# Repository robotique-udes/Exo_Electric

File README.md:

# Description
Ce répertoire regroupe les différents PCB de l'exosquelette au fil des compétitions. Il vise aussi à standardiser la création des schémas électriques ainsi que des PCB afin de les rendre plus lisibles et plus faciles à réviser et consulter. Les PCB avant 2026 ne suivent pas nécessairement le standard.

# Structure du repo
```
main
├── ACE2027/
│   ├── README.md
│   ├── Schéma-bloc
│   └── PCB1/
│       ├── README.md
│       ├── Schéma-bloc
│       │   ├── V1_0/
│       │   │   └── Fichiers KiCad
│       │   ├── V1_1/
│       │   │   ├── README.md
│       │   │   └── Fichiers KiCad
│       │   └── V2_0/
│       │       ├── README.md
│       │       └── Fichiers KiCad
│       └── PCB2/
│           └── (Même structure que PCB1)
└── ACE2028
    └── (Même structure que ACE 2027)
```
- Un dossier est créé pour chaque année de compétition
    - Contient un README.md décrivant le fonctionnement global du système électrique et présentant le schéma-bloc
    - Contient le schéma-bloc en image et dans son format original décrivant l'interaction entre les sous-systèmes électriques
    - Un dossier est créé par PCB
        - Contient un README.md qui explique le fonctionnement du PCB, contient les calculs et hypothèse fait pour le pcb et présente le schéma-bloc. Le README.md doit dire où se trouve le contour du pcb s'il a été fait sur ONSHAPE
        - Contient le schéma-bloc en image et dans son format original décrivant l'interaction entre les modules du PCB
            - Un dossier est fait pour chaque version du PCB.
                - La version 1_0 n'a pas besoin de README, mais les versions subséquentes devront en avoir un qui décrit les changements par rapport à la version antérieure.
                - Contient tous les fichiers KiCad

# Branches
Une branche est créée pour chaque PCB. <br>
Cette branche doit contenir le nom du PCB ainsi que sa version et le déroulement de la vie de cette branche se déroule ainsi:
1. Si le pcb est particuliairement complexe, écrire le readme et le shéma bloc qui défini ce que le PCB fait et comment il va le faire
2. Création d'une pull request vers le main afin de faire validé le fonctionnement du PCB
    - Faire les correctifs et demander à nouveau la vérification
3. Création du schéma électrique
4. Création d'une pull request vers le main afin de faire vérifier le schéma
    - Faire les correctifs et demander à nouveau la vérification
5. Création du PCB
6. Création d'une pull request vers le main afin de faire vérifier le PCB
    - Faire les correctifs et demander à nouveau la vérification
7. Suppression de la branche une fois le PCB commandé

## Convention de versions:
- V1.0  Premier prototype
- V1.X  Corrections mineures qui ne demandent pas de recommander le PCB
- VX.0  Révision majeure qui demande de recommander le PCB
- Chaque révision doit être documentée dans le README avec une explication claire des changements par rapport à la version précédente.

# Autres
**Il est très important de sauvegarder les fichiers et de fermer KiCad avant chaque commit**

# Standards à respecter
Les standards pour le schéma électrique se trouvent [ici](guideSchema.md) <br>
Les standards pour le PCB se trouvent [ici](guidePCB.md) <br>
Ces standards doivent être consultés et compris avant d'entamer le travail sur un schéma ou sur un PCB

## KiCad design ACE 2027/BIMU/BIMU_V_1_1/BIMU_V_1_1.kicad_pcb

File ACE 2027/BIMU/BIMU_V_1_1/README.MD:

## Update
* V1.1 
    inversé le RX et TX pour le CAN pour respecté les norme
    rajout une switch pour mettre ou retirer la therminaison CAN
    Connecté les deux pin de puissance du esp-32 qui doivent être connecté 
    fixer le silkscreen
    Rajouté des diodes pour évité le back feed dans le port USB

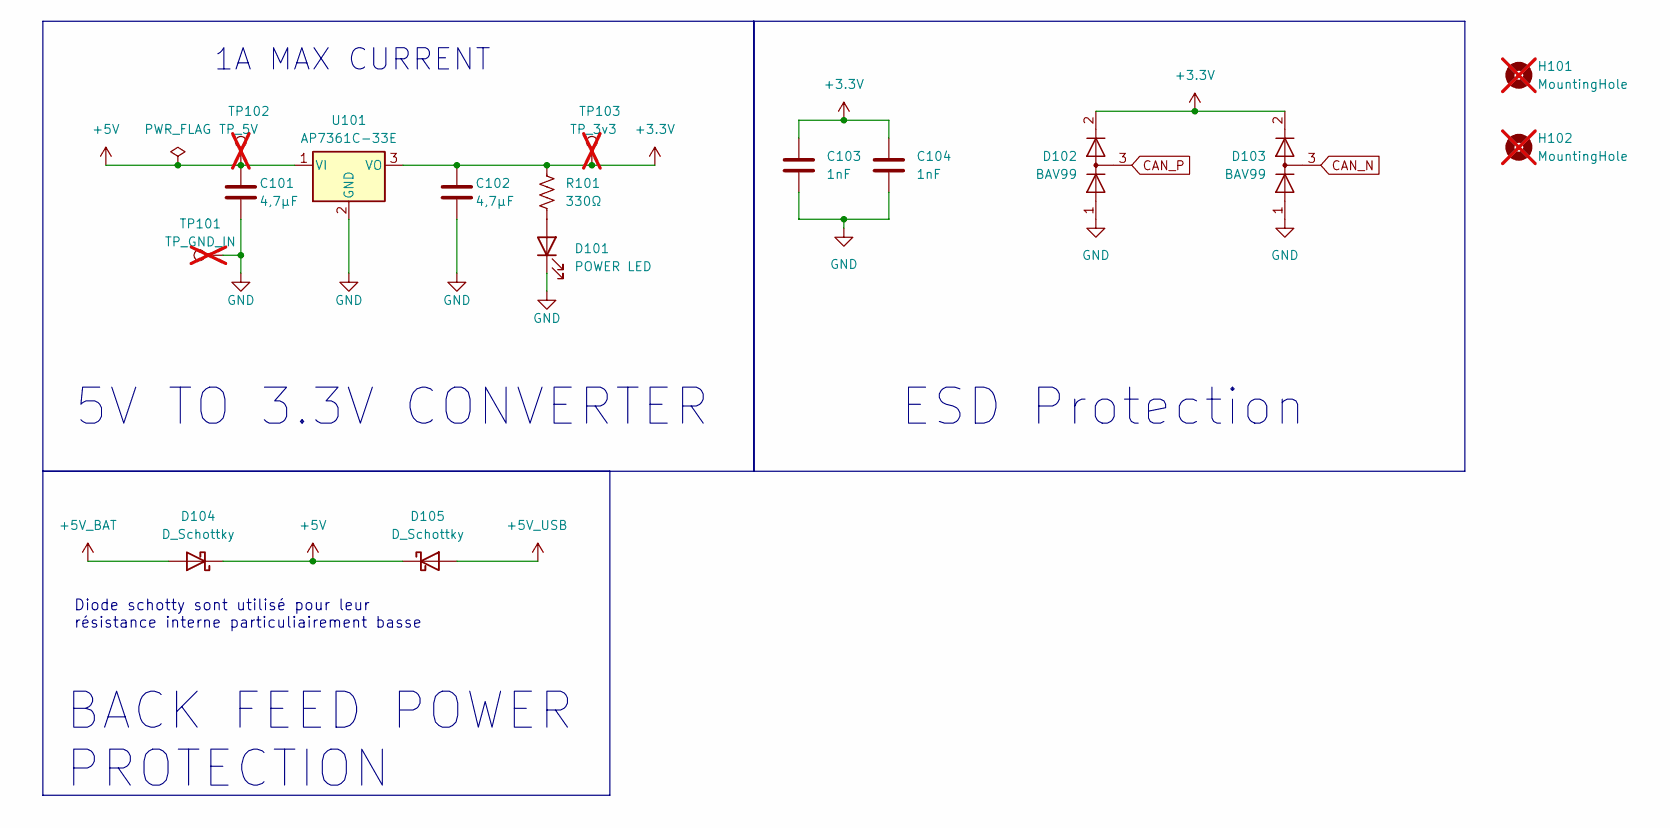
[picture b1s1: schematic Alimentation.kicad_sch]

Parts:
C101, C102: 4,7µF; C_0805_2012Metric_Pad1.18x1.45mm_HandSolder; Digi-Key_PN 1276-2970-1-ND
C103, C104: 1nF; C_1812_4532Metric_Pad1.57x3.40mm_HandSolder; Digi-Key_PN 399-C1812C104MDRACTUCT-ND
D101: POWER LED; LED_0805_2012Metric_Pad1.15x1.40mm_HandSolder; Digi-Key_PN 1516-QBLP631-IG5CT-ND
D102, D103: BAV99; SOT-23; Digi-Key_PN 1655-BAV99CT-ND
D104, D105: D_Schottky; D_0805_2012Metric_Pad1.15x1.40mm_HandSolder; Digi-Key_PN 478-7800-1-ND
H101, H102: MountingHole; MountingHole_3.2mm_M3_ISO14580; not fitted
R101: 330Ω; R_0805_2012Metric_Pad1.20x1.40mm_HandSolder; Digi-Key_PN 541-4168-1-ND
TP101: TP_GND_IN; TestPoint_Pad_1.0x1.0mm; not fitted
TP102: TP_5V; TestPoint_Pad_1.0x1.0mm; not fitted
TP103: TP_3v3; TestPoint_Pad_1.0x1.0mm; not fitted
U101: AP7361C-33E; SOT-223-3_TabPin2; Digi-Key_PN AP7361C-33E-13DICT-ND

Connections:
+3.3V: C102.2, C103.1, C104.1, D102.2 (A), D103.2 (A), R101.1, TP103.1 (1_1), U101.3 (VO); also elsewhere on the board
+5V: C101.2, D104.1 (K), D105.1 (K), TP102.1 (1_1), U101.1 (VI); also elsewhere on the board
+5V_BAT: D104.2 (A); also elsewhere on the board
+5V_USB: D105.2 (A); also elsewhere on the board
CAN_N: D103.3 (K); also elsewhere on the board
CAN_P: D102.3 (K); also elsewhere on the board
GND: C101.1, C102.1, C103.2, C104.2, D101.1 (K), D102.1 (K), D103.1 (K), TP101.1 (1_1), U101.2 (GND); also elsewhere on the board
unnamed: D101.2 (A), R101.2

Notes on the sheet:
Diode schotty sont utilisé pour leur résistance interne particuliairement basse
BACK FEED POWER PROTECTION
ESD Protection
1A MAX CURRENT
5V TO 3.3V CONVERTER

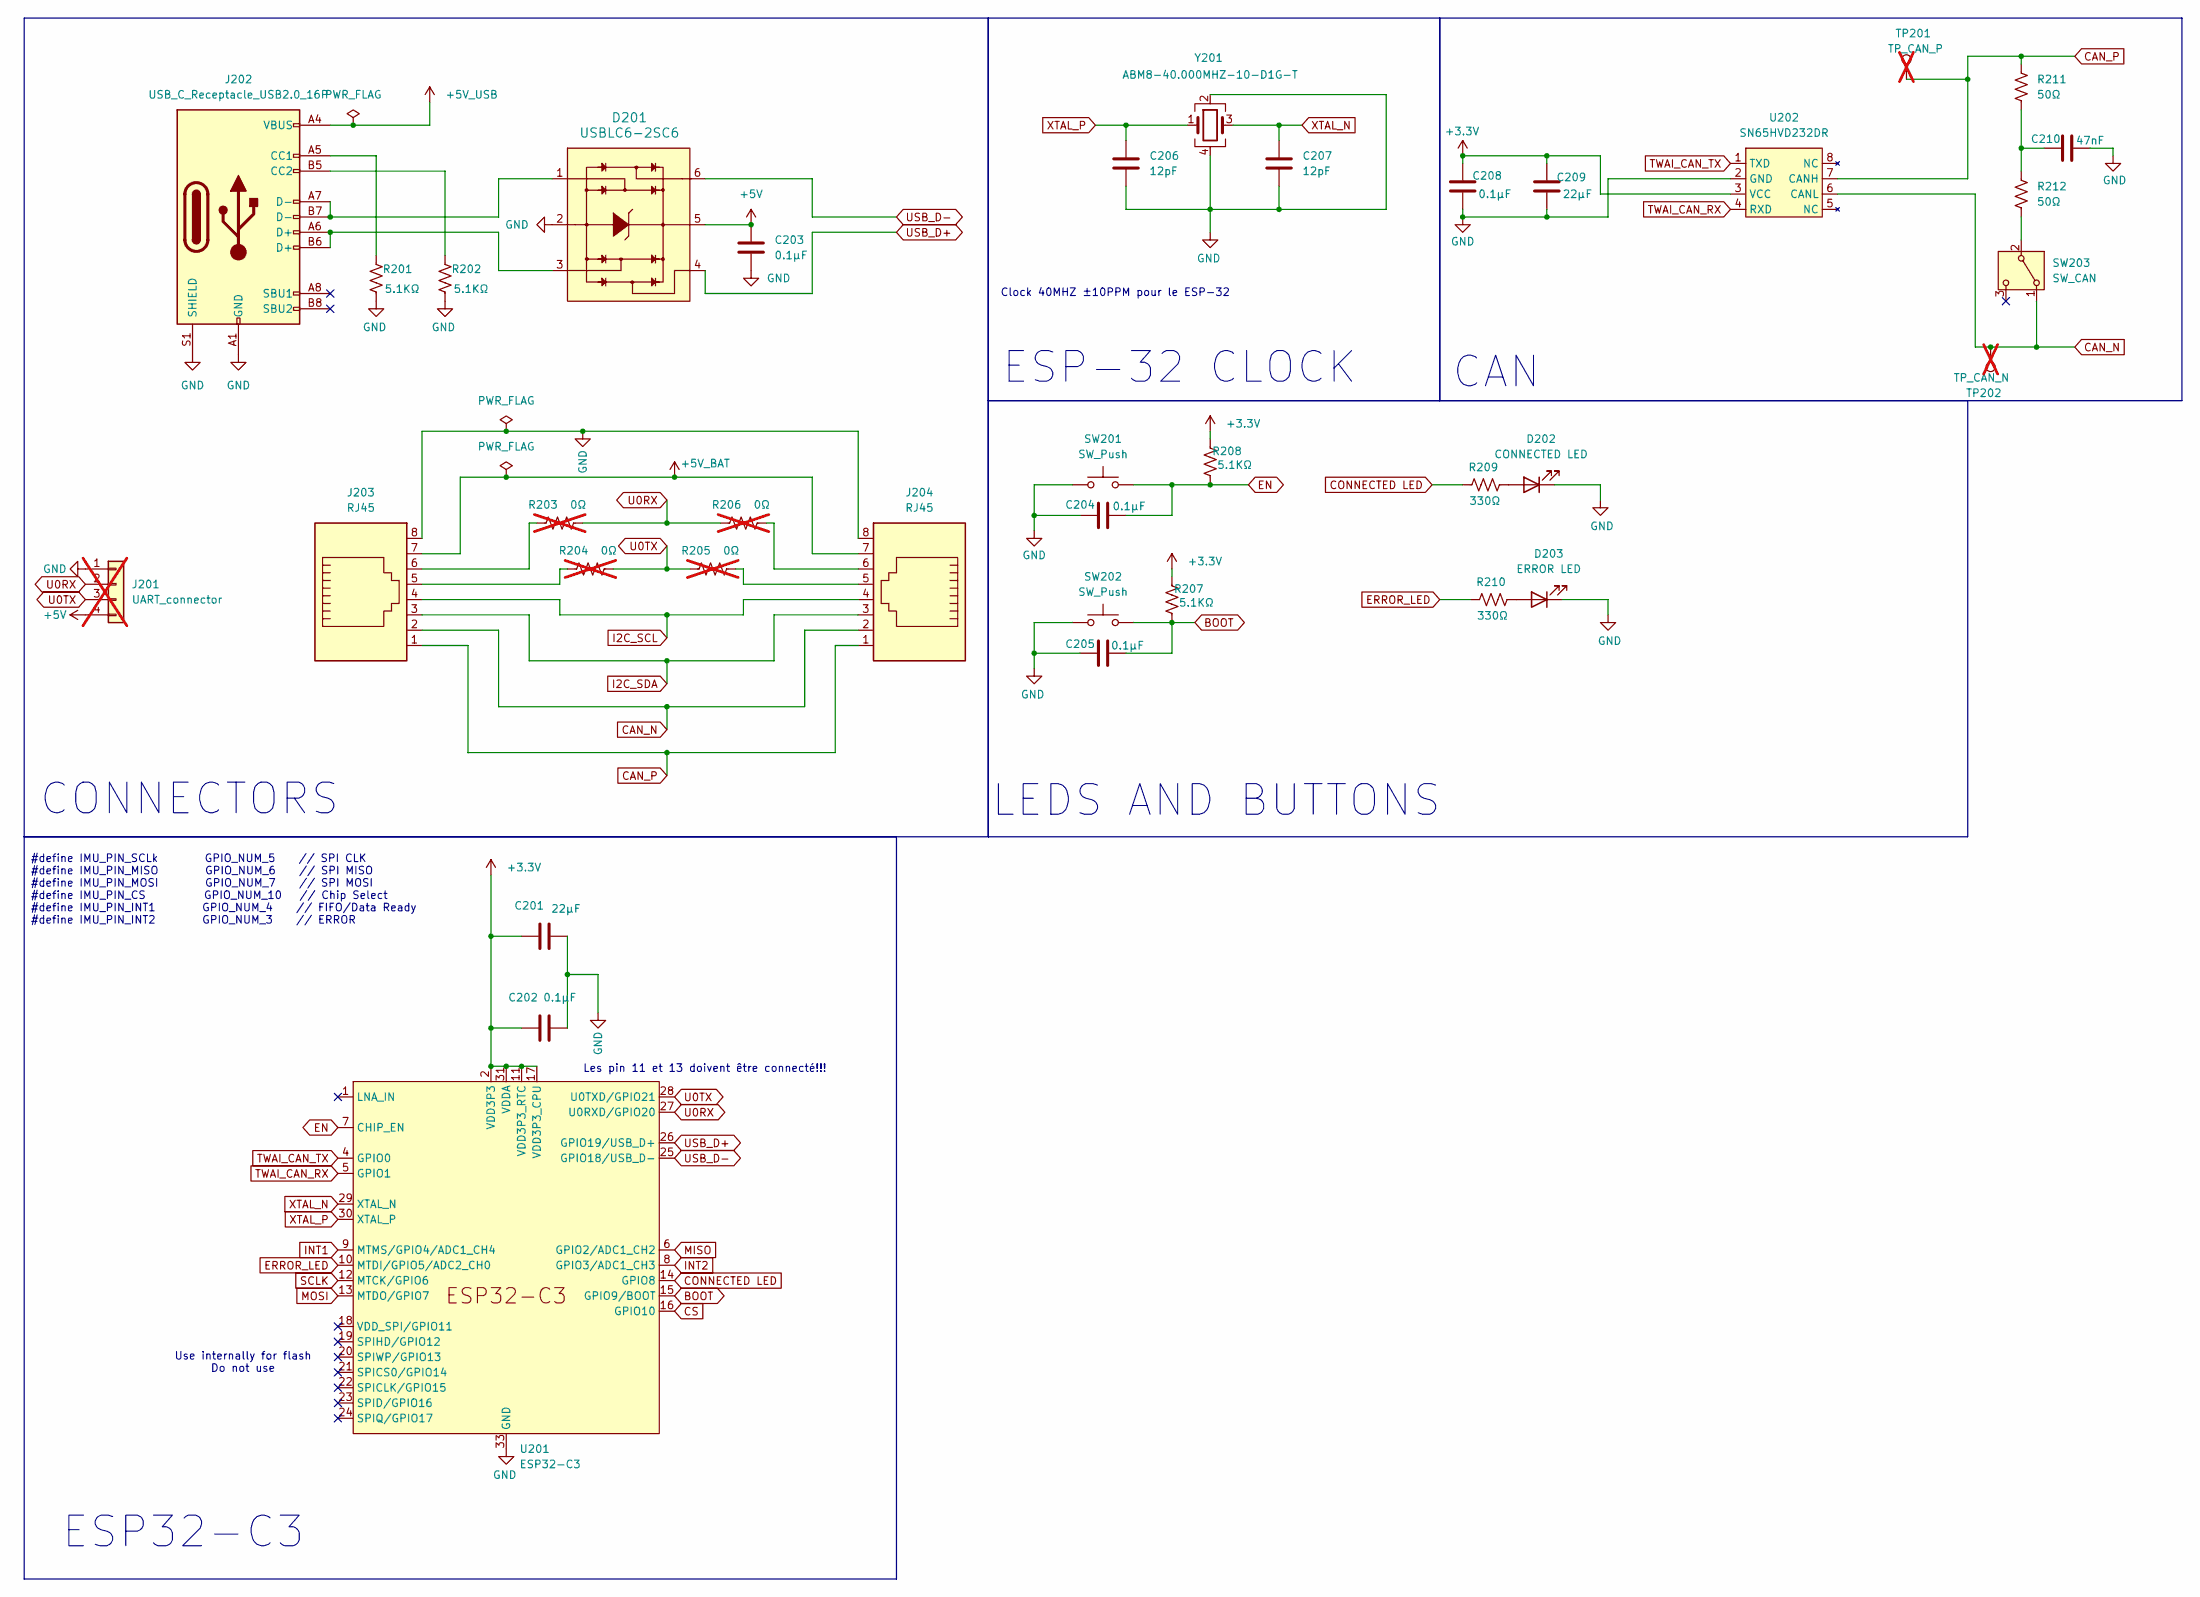
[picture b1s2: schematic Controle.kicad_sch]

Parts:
C201, C209: 22μF; C_0805_2012Metric_Pad1.18x1.45mm_HandSolder; Digi-Key_PN 1276-6501-1-ND
C202, C203, C204, C205, C208: 0.1μF; C_0805_2012Metric_Pad1.18x1.45mm_HandSolder; Digi-Key_PN 399-C0805C104K5RACTUCT-ND
C206, C207: 12pF; C_0805_2012Metric_Pad1.18x1.45mm_HandSolder; Digi-Key_PN 399-C0805C120J8HACTUCT-ND
C210: 47nF; C_0603_1608Metric_Pad1.08x0.95mm_HandSolder; Digi-Key_PN 1276-2960-1-ND
D201: USBLC6-2SC6; SOT23-6L; MPN USBLC6-2SC6; Digi-Key_PN 4518-USBLC6-2SC6CT-ND
D202: CONNECTED LED; LED_0805_2012Metric_Pad1.15x1.40mm_HandSolder; Digi-Key_PN 1516-QBLP631-IB5CT-ND
D203: ERROR LED; LED_0805_2012Metric_Pad1.15x1.40mm_HandSolder; Digi-Key_PN 1516-QBLP631-R5-2897CT-ND
J201: UART_connector; PinSocket_1x04_P2.54mm_Vertical; not fitted
J202: USB_C_Receptacle_USB2.0_16P; USB_C_Receptacle_GCT_USB4105-xx-A_16P_TopMnt_Horizontal; Digi-Key_PN 2073-USB4105-GF-ACT-ND
J203, J204: RJ45; RJ45_Amphenol_54602-x08_Horizontal; Digi-Key_PN 609-1046-ND
R201, R202, R207, R208: 5.1KΩ; R_0805_2012Metric_Pad1.20x1.40mm_HandSolder; Digi-Key_PN 541-CRCW08055K10FKEACCT-ND
R203, R204, R205, R206: 0Ω; R_0402_1005Metric_Pad0.72x0.64mm_HandSolder; not fitted
R209, R210: 330Ω; R_0805_2012Metric_Pad1.20x1.40mm_HandSolder; Digi-Key_PN 541-4168-1-ND
R211, R212: 50Ω; R_0805_2012Metric_Pad1.20x1.40mm_HandSolder; Digi-Key_PN 541-CRCW080550R0FKTACT-ND
SW201, SW202: SW_Push; SW_SPST_B3U-1000P; Digi-Key_PN SW1021CT-ND
SW203: SW_CAN; SW_SPDT_CK_JS102011SAQN; Digi-Key_PN 401-1999-1-ND
TP201: TP_CAN_P; TestPoint_Pad_1.0x1.0mm; not fitted
TP202: TP_CAN_N; TestPoint_Pad_1.0x1.0mm; not fitted
U201: ESP32-C3; QFN-32-1EP_5x5mm_P0.5mm_EP3.45x3.45mm; Digi-Key_PN 1904-ESP32-C3FH4CT-ND
U202: SN65HVD232DR; SOIC-8_3.9x4.9mm_P1.27mm; Digi-Key_PN 296-26344-1-ND
Y201: ABM8-40.000MHZ-10-D1G-T; Crystal_SMD_2016-4Pin_2.0x1.6mm; Digi-Key_PN 535-14997-1-ND

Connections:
+3.3V: C201.1, C202.1, C208.1, C209.1, R207.2, R208.2, U201.2 (VDD3P3), U201.3 (VDD3P3), U201.11 (VDD3P3_RTC), U201.17 (VDD3P3_CPU), U201.31 (VDDA), U201.32 (VDDA), U202.3 (VCC); also elsewhere on the board
+5V: C203.1, D201.5, J201.4; also elsewhere on the board
+5V_BAT: J203.7, J204.7; also elsewhere on the board
+5V_USB: J202.A4 (VBUS), J202.A9 (VBUS), J202.B4 (VBUS), J202.B9 (VBUS); also elsewhere on the board
BOOT: C205.1, R207.1, SW202.2, U201.15 (GPIO9/BOOT)
CAN_N: J203.2, J204.2, SW203.1 (A), TP202.1 (1_1), U202.6 (CANL); also elsewhere on the board
CAN_P: J203.1, J204.1, R211.1, TP201.1 (1_1), U202.7 (CANH); also elsewhere on the board
CONNECTED LED: R209.2, U201.14 (GPIO8)
CS: U201.16 (GPIO10); also elsewhere on the board
EN: C204.1, R208.1, SW201.2, U201.7 (CHIP_EN)
ERROR_LED: R210.2, U201.10 (MTDI/GPIO5/ADC2_CH0)
GND: C201.2, C202.2, C203.2, C204.2, C205.2, C206.2, C207.2, C208.2, C209.2, C210.1, D201.2, D202.1 (K), D203.1 (K), J201.1, J202.A1 (GND), J202.A12 (GND), J202.B1 (GND), J202.B12 (GND), J202.S1 (SHIELD), J203.8, J204.8, R201.2, R202.2, SW201.1, SW202.1, U201.33 (GND), U202.2 (GND), Y201.2, Y201.4; also elsewhere on the board
I2C_SCL: J203.4, J204.4
I2C_SDA: J203.3, J204.3
INT1: U201.9 (MTMS/GPIO4/ADC1_CH4); also elsewhere on the board
INT2: U201.8 (GPIO3/ADC1_CH3); also elsewhere on the board
MISO: U201.6 (GPIO2/ADC1_CH2); also elsewhere on the board
MOSI: U201.13 (MTDO/GPIO7); also elsewhere on the board
unnamed: C210.2, R211.2, R212.1
unnamed: D201.1, J202.A7 (D-), J202.B7 (D-)
unnamed: D201.3, J202.A6 (D+), J202.B6 (D+)
unnamed: D202.2 (A), R209.1
unnamed: D203.2 (A), R210.1
unnamed: J202.A5 (CC1), R201.1
unnamed: J202.B5 (CC2), R202.1
unnamed: J203.5, R204.1
unnamed: J203.6, R203.1
unnamed: J204.5, R205.2
unnamed: J204.6, R206.2
unnamed: R212.2, SW203.2 (B)
SCLK: U201.12 (MTCK/GPIO6); also elsewhere on the board
TWAI_CAN_RX: U201.5 (GPIO1), U202.4 (RXD)
TWAI_CAN_TX: U201.4 (GPIO0), U202.1 (TXD)
U0RX: J201.2, R203.2, R206.1, U201.27 (U0RXD/GPIO20)
U0TX: J201.3, R204.2, R205.1, U201.28 (U0TXD/GPIO21)
USB_D+: D201.4, U201.26 (GPIO19/USB_D+)
USB_D-: D201.6, U201.25 (GPIO18/USB_D-)
XTAL_N: C207.1, U201.29 (XTAL_N), Y201.3
XTAL_P: C206.1, U201.30 (XTAL_P), Y201.1

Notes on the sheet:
ESP32-C3
Les pin 11 et 13 doivent être connecté!!!
#define IMU_PIN_SCLk GPIO_NUM_5 // SPI CLK #define IMU_PIN_MISO GPIO_NUM_6 // SPI MISO #define IMU_PIN_MOSI GPIO_NUM_7 // SPI MOSI #define IMU_PIN_CS GPIO_NUM_10 // Chip Select #define IMU_PIN_INT1 GPIO_NUM_4 // FIFO/Data Ready #define IMU_PIN_INT2 GPIO_NUM_3 // ERROR
CONNECTORS
Use internally for flash Do not use
ESP-32 CLOCK
LEDS AND BUTTONS
CAN
Clock 40MHZ ±10PPM pour le ESP-32

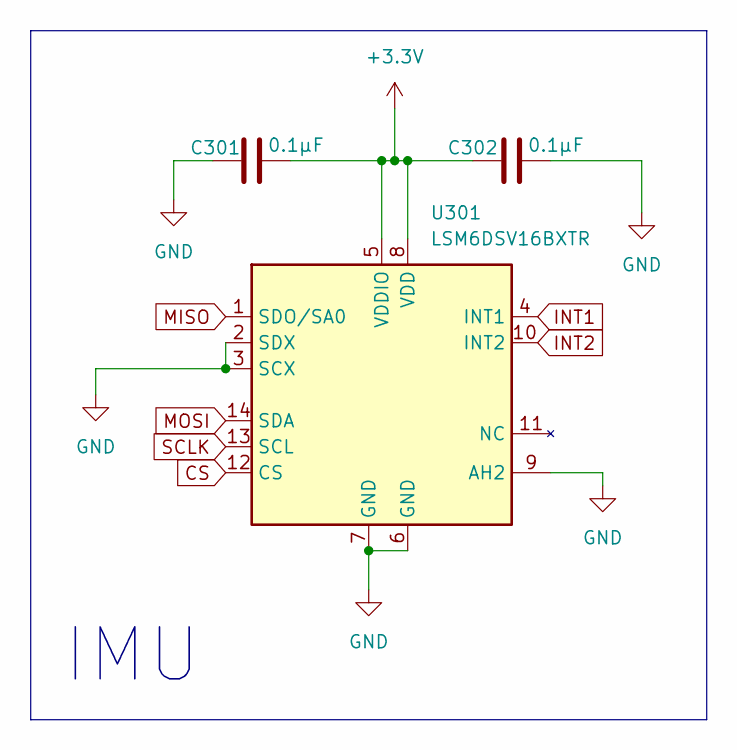
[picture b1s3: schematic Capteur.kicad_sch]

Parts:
C301, C302: 0.1μF; C_0805_2012Metric_Pad1.18x1.45mm_HandSolder; Digi-Key_PN 399-C0805C104K5RACTUCT-ND
U301: LSM6DSV16BXTR; LGA-14_3x2.5mm_P0.5mm_LayoutBorder3x4y; Digi-Key_PN 497-LSM6DSV16BXTRCT-ND

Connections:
+3.3V: C301.1, C302.2, U301.5 (VDDIO), U301.8 (VDD); also elsewhere on the board
CS: U301.12 (CS); also elsewhere on the board
GND: C301.2, C302.1, U301.2 (SDX), U301.3 (SCX), U301.6 (GND), U301.7 (GND), U301.9 (AH2); also elsewhere on the board
INT1: U301.4 (INT1); also elsewhere on the board
INT2: U301.10 (INT2); also elsewhere on the board
MISO: U301.1 (SDO/SA0); also elsewhere on the board
MOSI: U301.14 (SDA); also elsewhere on the board
SCLK: U301.13 (SCL); also elsewhere on the board

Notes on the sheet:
IMU

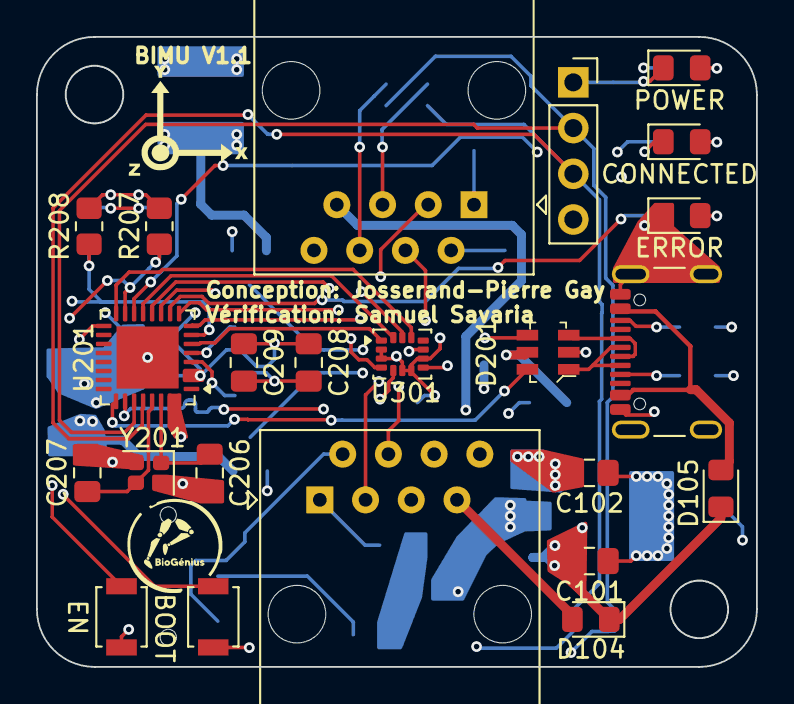
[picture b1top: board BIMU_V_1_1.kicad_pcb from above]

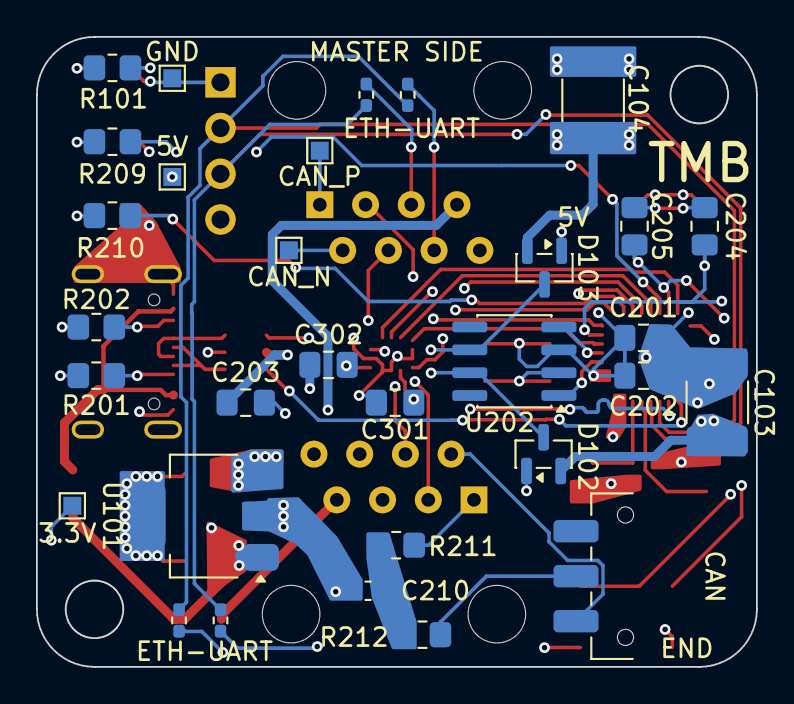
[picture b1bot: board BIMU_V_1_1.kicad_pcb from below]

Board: 4 copper layers, 40.0 x 35.0 mm, 56 parts (31 on the bottom side), 40 nets.

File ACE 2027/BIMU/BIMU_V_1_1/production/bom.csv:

Designator,Footprint,Quantity,Value,LCSC Part #
"C101, C102",0805,2,"4,7µF",
"C103, C104",1812,2,1nF,
"C201, C209",0805,2,22μF,
"C202, C203, C204, C205, C208, C301, C302",0805,7,0.1μF,
"C206, C207",0805,2,12pF,
C210,0603,1,47nF,
D101,0805,1,POWER LED,
"D102, D103",SOT-23,2,BAV99,
"D104, D105",0805,2,D_Schottky,
D201,SOT23-6L,1,USBLC6-2SC6,USBLC6-2SC6
D202,0805,1,CONNECTED LED,
D203,0805,1,ERROR LED,
J202,USB_C_Receptacle_GCT_USB4105-xx-A_16P_TopMnt_Horizontal,1,USB_C_Receptacle_USB2.0_16P,
"J203, J204",RJ45_Amphenol_54602-x08_Horizontal,2,RJ45,
"R101, R209, R210",0805,3,330Ω,
"R201, R202, R207, R208",0805,4,5.1KΩ,
"R203, R204, R205, R206",0402,4,0Ω,
"R211, R212",0805,2,50Ω,
"SW201, SW202",SW_SPST_B3U-1000P,2,SW_Push,
SW203,SW_SPDT_CK_JS102011SAQN,1,SW_CAN,
TP101,TestPoint_Pad_1.0x1.0mm,1,TP_GND_IN,
TP102,TestPoint_Pad_1.0x1.0mm,1,TP_5V,
TP103,TestPoint_Pad_1.0x1.0mm,1,TP_3v3,
TP201,TestPoint_Pad_1.0x1.0mm,1,TP_CAN_P,
TP202,TestPoint_Pad_1.0x1.0mm,1,TP_CAN_N,
U101,SOT-223-3_TabPin2,1,AP7361C-33E,
U201,QFN-32-1EP_5x5mm_P0.5mm_EP3.45x3.45mm,1,ESP32-C3,
U202,SOIC-8_3.9x4.9mm_P1.27mm,1,SN65HVD232DR,
U301,LGA-14_3x2.5mm_P0.5mm_LayoutBorder3x4y,1,LSM6DSV16BXTR,
Y201,Crystal_SMD_2016-4Pin_2.0x1.6mm,1,ABM8-40.000MHZ-10-D1G-T,

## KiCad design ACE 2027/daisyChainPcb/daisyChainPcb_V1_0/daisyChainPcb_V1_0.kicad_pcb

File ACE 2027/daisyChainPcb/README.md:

# PCB daisy chain

Ce PCB permet de passer les alimentations et les signaux de l'exo à travers celui-ci à la chaîne afin d'éviter les câbles superflus. Il sera sur les moteurs et permettra en même temps la communication et l'alimenation de ceux-ci.

## Objectifs
- Passer l'alimentation 48V d'un côté du PCB à l'autre
- Alimenter les moteurs
- Passer l'alimentation 5V d'un côté du PCB à l'autre
- Alimenter une puce permettant la conversion du 5V au 3.3V pour la communication I2C
- Remettre à niveau le signal I2C afin de s'assurer de sa bonne transmission
- Le rendre compatible avec l'exo 2026 et 2027
    - Être capable de passer la communication CAN tout en gardant la communication I2C au cas où elle doit être utilisé
- Se monter sur les moteurs de facon compacte et fiable
- Transmettre le signal UART (RX/TX) afin de communiquer de cette méthode avec les moteurs si c'est nécessaire (Certaines données peuvent être récuperer seulement dans un mode de communication et non l'autre)

## Conception

### Alimentation
Ce PCB doit gérer à la fois une alimentation de 48V et de 5V. Il y a deux grounds séparé. Le premier est celui de l'alimentation 48V et le deuxième est celui de l'alimentation de 5V. Le PCB a deux ground planes qui sont associés avec l'alimentation 5V. Cette décision a été prise afin de s'assurer de l'intégrité des signaux en donnant la plus grande surface de ground pour le circuit qui transporte les signaux. Ainsi, le ground lié à l'alimentation 48V est seulement connecté par des traces normales. La séparation de ces deux grounds permet aussi de s'assurer de ne pas avoir de tensions parasites qui passent par les IMU ou autre processeurs plus sensibles et évite donc de les détruire.

La communication I2C se fait à une tension de 3.3V. Il y a donc, sur le PCB, un convertisseur DC/DC qui transforme la tension de 5V vers 3.3V. Cette tension est ensuite envoyé vers les signaux I2C à travers une résistance de 1k.

### Disposition du PCB et choix de conception
Le PCB s'attache aux moteurs du côté des connecteurs de ce dernier. Il est donc important qu'il soit assez petit pour ne pas gêner aux mouvements de l'utilisateur. C'est pourquoi il n'y a pas de connecteurs pour l'alimentation et les signaux du côté du PCB. Seulement des beignes sont présents afin de souder des fils qui, eux, auront un connecteur au bout afin de se connecter aux moteurs.

Nous avons deux ground planes pour l'alimentation de 5V qui ont pleins de vias afin de bien connecter les deux planes ensemble.

Les traces qui transmettent les signaux sont le plus près possible l'un de l'autre et ont les mêmes longeurs. L'utilisation des vias a aussi été évité le plus possible.

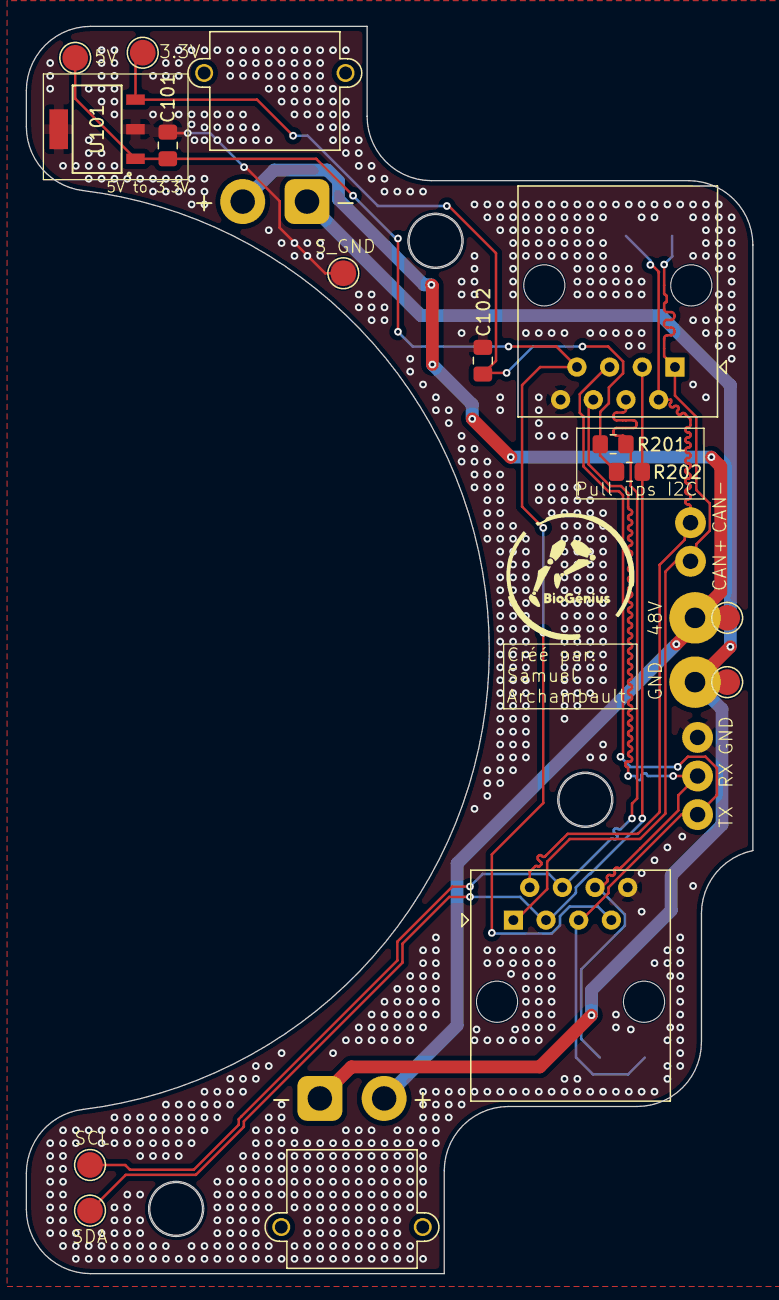
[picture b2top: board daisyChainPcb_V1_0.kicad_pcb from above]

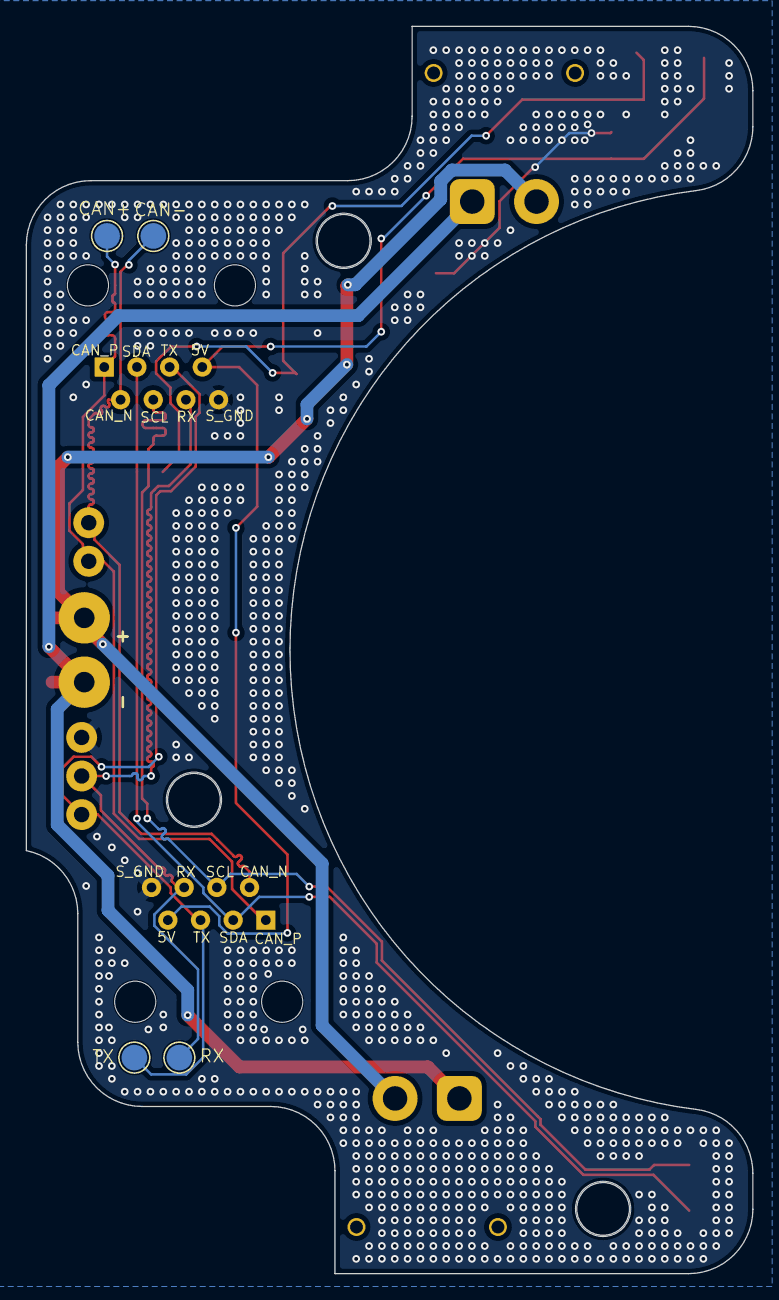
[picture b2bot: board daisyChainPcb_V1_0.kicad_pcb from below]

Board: 2 copper layers, 56.5 x 97.0 mm, 26 parts (4 on the bottom side), 11 nets.

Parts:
C101, C102: 4.7uF; C_0805_2012Metric_Pad1.18x1.45mm_HandSolder
H401, H402, H403: MountingHole; MountingHole_4.3mm_M4
J201: Pads; motorPads
J202, J203: XT30; AMASS_XT30PW-M_1x02_P2.50mm_Horizontal
J204: Pads; CAN_pads
J205: Pads; UART_pads
J206, J207: RJ45; RJ45_Amphenol_54602-x08_Horizontal
R201, R202: 1kΩ; R_0805_2012Metric_Pad1.20x1.40mm_HandSolder
TP201: CAN_P_TP; TestPoint_Pad_D2.0mm
TP202: SDA_TP; TestPoint_Pad_D2.0mm
TP203: CAN_N_TP; TestPoint_Pad_D2.0mm
TP204: SCL_TP; TestPoint_Pad_D2.0mm
TP205: TX_TP; TestPoint_Pad_D2.0mm
TP206: 5V_TP; TestPoint_Pad_D2.0mm
TP207: RX_TP; TestPoint_Pad_D2.0mm
TP208: GND_TP; TestPoint_Pad_D2.0mm
TP209: 48V_TP; TestPoint_Pad_D2.0mm
TP210: Power_GND_TP; TestPoint_Pad_D2.0mm
TP211: 3V3_TP; TestPoint_Pad_D2.0mm
U101: AP7361C-33E-13; SOT223_DIO-L

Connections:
+5V: C101.1, J206.7, J207.7, TP206.1 (1_1), U101.1 (IN)
+48V: J201.2, J202.2, J203.2, TP209.1 (1_1)
/Controle/CAN_N: J204.1, J206.2, J207.2, TP203.1 (1_1)
/Controle/CAN_P: J204.2, J206.1, J207.1, TP201.1 (1_1)
/Controle/RX: J205.2, J206.6, J207.6, TP207.1 (1_1)
/Controle/SCL: J206.4, J207.4, R201.1, TP204.1 (1_1)
/Controle/SDA: J206.3, J207.3, R202.1, TP202.1 (1_1)
/Controle/TX: J205.1, J206.5, J207.5, TP205.1 (1_1)
VCC_3V3: C102.1, R201.2, R202.2, TP211.1 (1_1), U101.3 (OUT)
power_GND: J201.1, J202.1, J203.1, TP210.1 (1_1)
signal_GND: C101.2, C102.2, J205.3, J206.8, J207.8, TP208.1 (1_1), U101.2 (GND), U101.4 (GND)

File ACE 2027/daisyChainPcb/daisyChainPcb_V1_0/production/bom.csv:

Designator,Footprint,Quantity,Value,LCSC Part #
"C101, C102",0805,2,4.7uF,
J201,motorPads,1,Pads,
"J202, J203",AMASS_XT30PW-M_1x02_P2.50mm_Horizontal,2,XT30,
J204,CAN_pads,1,Pads,
J205,UART_pads,1,Pads,
"J206, J207",RJ45_Amphenol_54602-x08_Horizontal,2,RJ45,
"R201, R202",0805,2,1kΩ,
TP201,TestPoint_Pad_D2.0mm,1,CAN_P_TP,
TP202,TestPoint_Pad_D2.0mm,1,SDA_TP,
TP203,TestPoint_Pad_D2.0mm,1,CAN_N_TP,
TP204,TestPoint_Pad_D2.0mm,1,SCL_TP,
TP205,TestPoint_Pad_D2.0mm,1,TX_TP,
TP206,TestPoint_Pad_D2.0mm,1,5V_TP,
TP207,TestPoint_Pad_D2.0mm,1,RX_TP,
TP208,TestPoint_Pad_D2.0mm,1,GND_TP,
TP209,TestPoint_Pad_D2.0mm,1,48V_TP,
TP210,TestPoint_Pad_D2.0mm,1,Power_GND_TP,
TP211,TestPoint_Pad_D2.0mm,1,3V3_TP,
U101,SOT223_DIO-L,1,AP7361C-33E-13,
